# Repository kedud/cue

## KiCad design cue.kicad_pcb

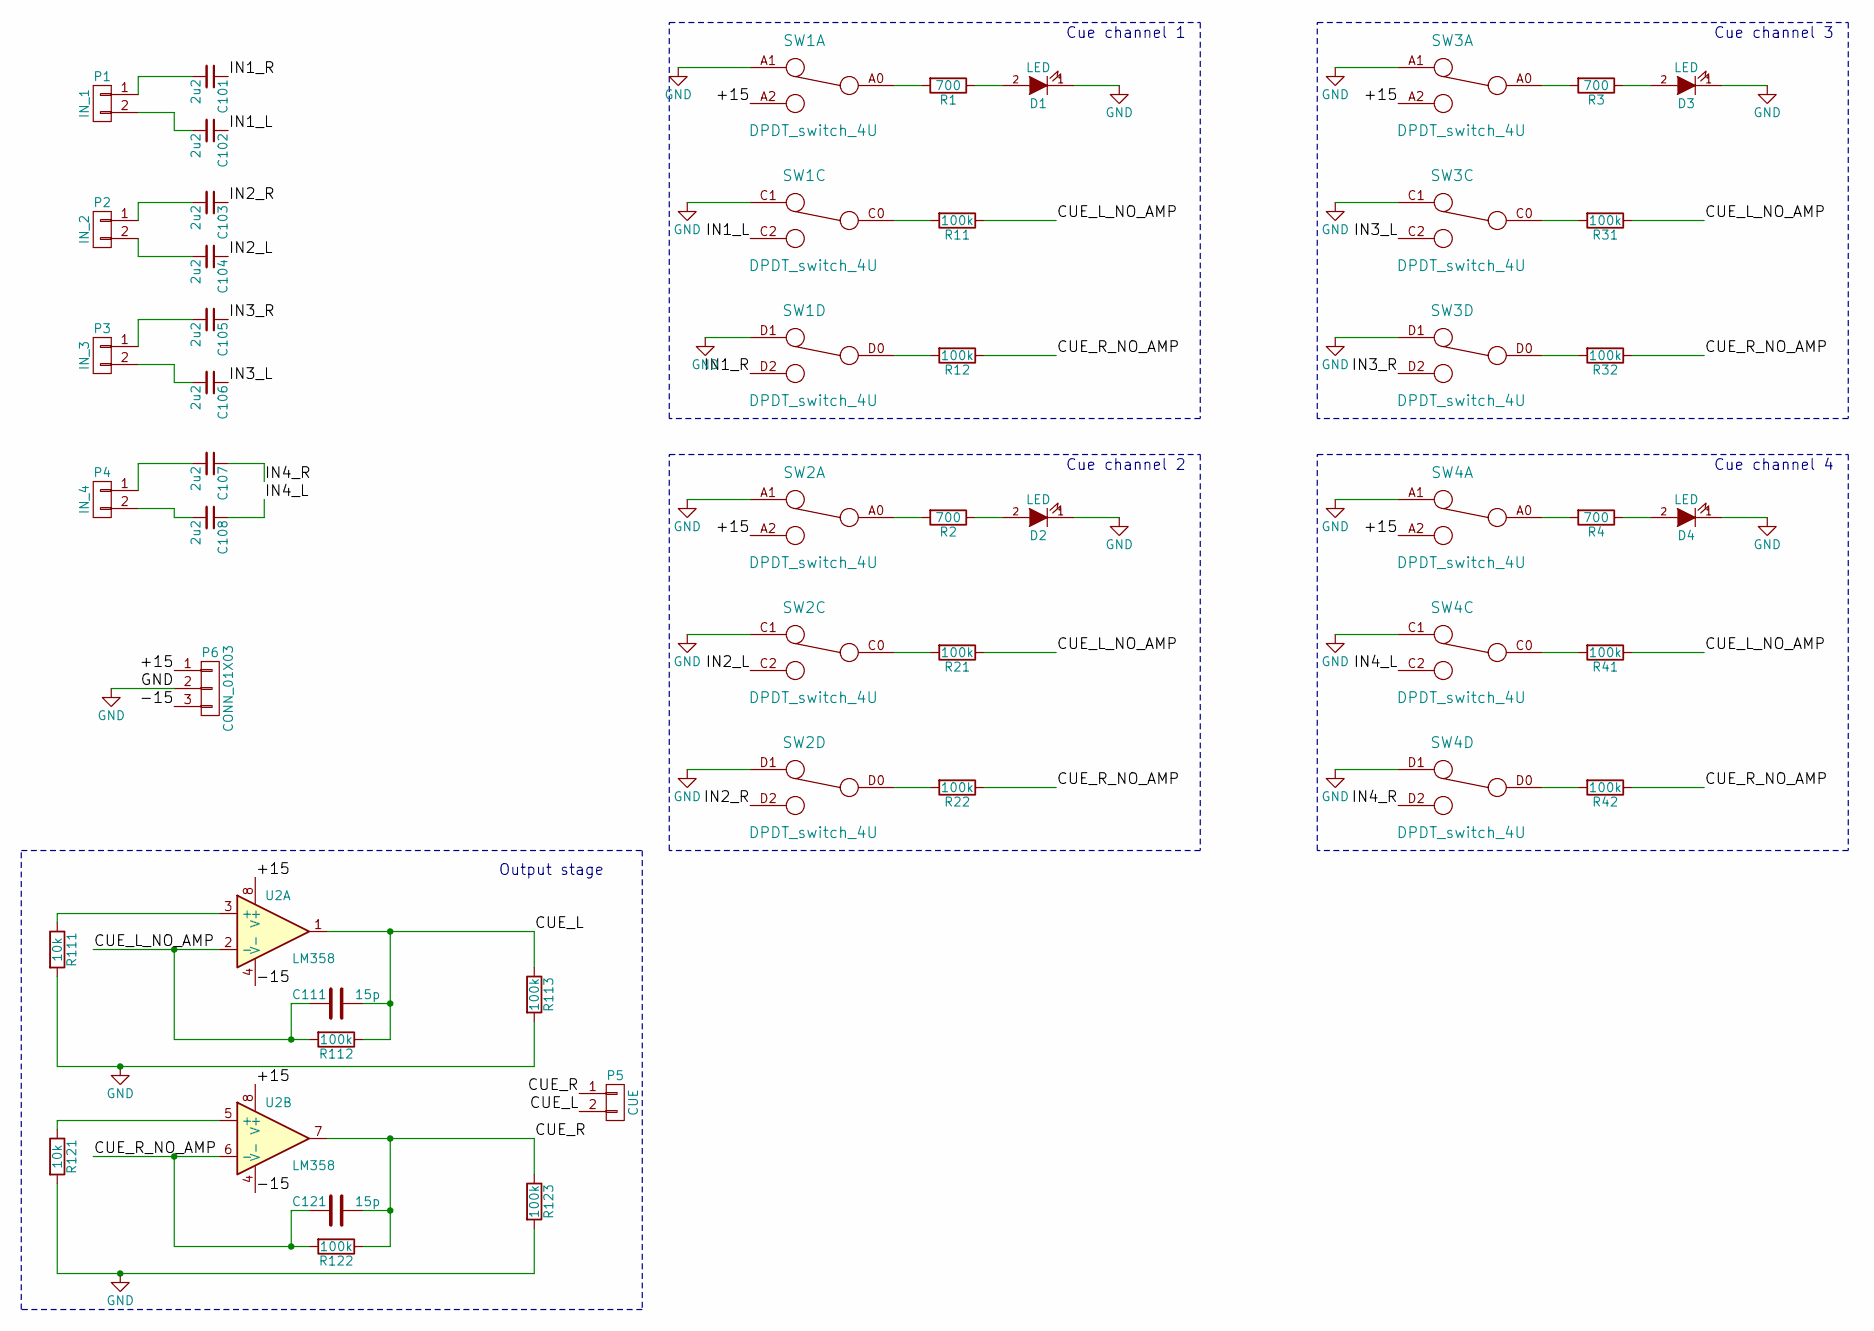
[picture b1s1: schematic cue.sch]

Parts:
C101, C102, C103, C104, C105, C106, C107, C108: 2u2; C_Rect_L7.2mm_W2.5mm_P5.00mm_FKS2_FKP2_MKS2_MKP2; Mfg_Part_No RSBCC4220Z310K; Mouser Digikey
C111, C121: 15p; C_Disc_D3_P2.5
D1: LED; LED_D5.0mm_Horizontal_O6.35mm_Z9.0mm; Mfg_Part_No 0
D2, D3, D4: LED; LED_D5.0mm_Horizontal_O6.35mm_Z9.0mm
P1: IN_1; Pin_Header_Angled_1x02
P2: IN_2; Pin_Header_Angled_1x02
P3: IN_3; Pin_Header_Angled_1x02
P4: IN_4; Pin_Header_Angled_1x02
P5: CUE; Pin_Header_Angled_1x02
P6: CONN_01X03; Pin_Header_Angled_1x03
R1, R2, R3, R4: 700; R_Axial_DIN0204_L3.6mm_D1.6mm_P5.08mm_Horizontal
R11, R12, R21, R22, R31, R32, R41, R42, R112, R113, R122, R123: 100k; R_Axial_DIN0204_L3.6mm_D1.6mm_P5.08mm_Horizontal
R111, R121: 10k; R_Axial_DIN0204_L3.6mm_D1.6mm_P5.08mm_Horizontal
SW1: DPDT_switch_4U; Swith_F4UEE; Mfg_Part_No 0
SW2, SW3, SW4: DPDT_switch_4U; Swith_F4UEE; Mfg_Part_No F4UEE
U2: LM358; DIP-8_W7.62mm_LongPads

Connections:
/+15: P6.1, SW1.A2, SW2.A2, SW3.A2, SW4.A2, U2.8 (V+)
/-15: P6.3, U2.4 (V-)
/CUE_L: C111.1, P5.2, R112.1, R113.1, U2.1
/CUE_L_NO_AMP: C111.2, R11.1, R21.1, R31.1, R41.1, R112.2, U2.2 (-)
/CUE_R: C121.1, P5.1, R122.1, R123.1, U2.7
/CUE_R_NO_AMP: C121.2, R12.1, R22.1, R32.1, R42.1, R122.2, U2.6 (-)
/IN1_L: C102.1, SW1.C2
/IN1_R: C101.1, SW1.D2
/IN2_L: C104.1, SW2.C2
/IN2_R: C103.1, SW2.D2
/IN3_L: C106.1, SW3.C2
/IN3_R: C105.1, SW3.D2
/IN4_L: C108.1, SW4.C2
/IN4_R: C107.1, SW4.D2
GND: D1.1 (K), D2.1 (K), D3.1 (K), D4.1 (K), P6.2, R111.2, R113.2, R121.2, R123.2, SW1.A1, SW1.C1, SW1.D1, SW2.A1, SW2.C1, SW2.D1, SW3.A1, SW3.C1, SW3.D1, SW4.A1, SW4.C1, SW4.D1
unnamed: C101.2, P1.1
unnamed: C102.2, P1.2
unnamed: C103.2, P2.1
unnamed: C104.2, P2.2
unnamed: C105.2, P3.1
unnamed: C106.2, P3.2
unnamed: C107.2, P4.1
unnamed: C108.2, P4.2
unnamed: D1.2 (A), R1.1
unnamed: D2.2 (A), R2.1
unnamed: D3.2 (A), R3.1
unnamed: D4.2 (A), R4.1
unnamed: R1.2, SW1.A0
unnamed: R2.2, SW2.A0
unnamed: R3.2, SW3.A0
unnamed: R4.2, SW4.A0
unnamed: R11.2, SW1.C0
unnamed: R12.2, SW1.D0
unnamed: R21.2, SW2.C0
unnamed: R22.2, SW2.D0
unnamed: R31.2, SW3.C0
unnamed: R32.2, SW3.D0
unnamed: R41.2, SW4.C0
unnamed: R42.2, SW4.D0
unnamed: R111.1, U2.3 (+)
unnamed: R121.1, U2.5 (+)

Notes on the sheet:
Cue channel 1
Cue channel 2
Cue channel 3
Cue channel 4
Output stage

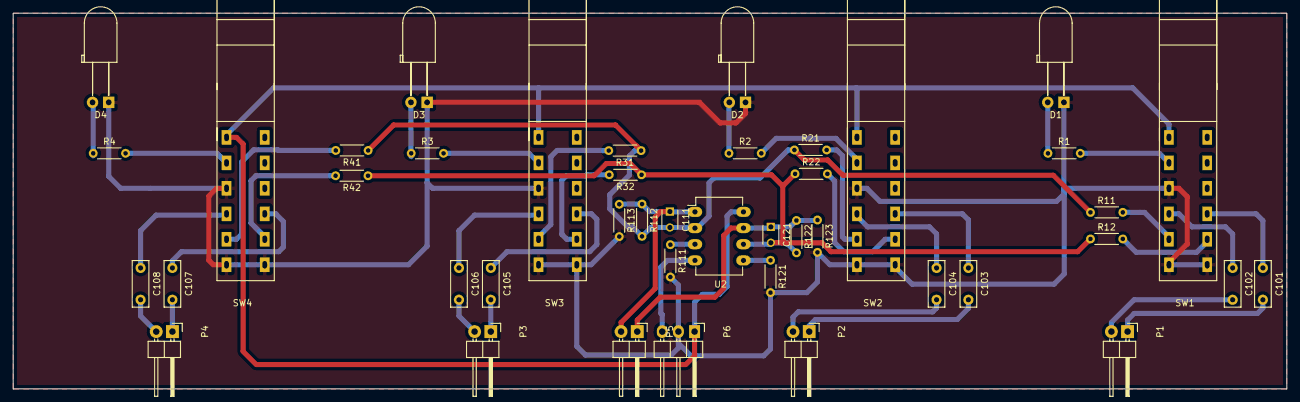
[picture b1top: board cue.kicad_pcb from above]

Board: 2 copper layers, 200.0 x 59.0 mm, 43 parts (0 on the bottom side), 41 nets.

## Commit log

2017-11-15 Add LEDs references
2017-11-16 Add components references
2017-12-25 Updating .gitignore to ignore 3D files
